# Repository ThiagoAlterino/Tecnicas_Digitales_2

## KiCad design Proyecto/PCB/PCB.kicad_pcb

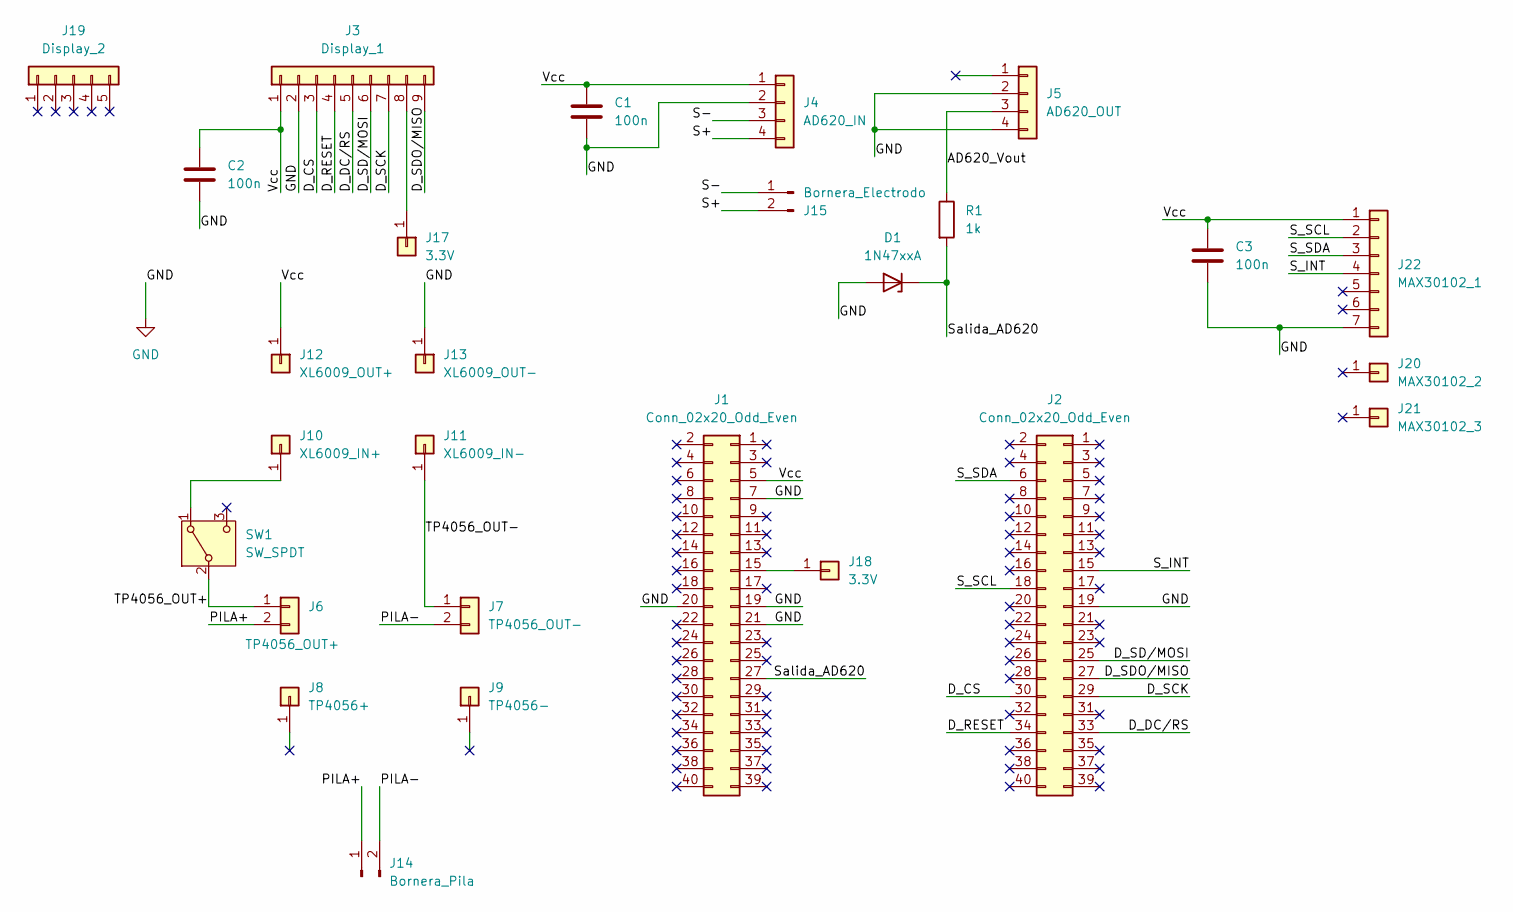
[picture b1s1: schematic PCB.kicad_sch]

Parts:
C1, C2, C3: 100n; C_Disc_D5.0mm_W2.5mm_P5.00mm
D1: 1N47xxA; D_DO-41_SOD81_P10.16mm_Horizontal
J1, J2: Conn_02x20_Odd_Even; PinSocket_2x20_P2.54mm_Vertical
J3: Display_1; PinSocket_1x09_P2.54mm_Vertical
J4: AD620_IN; PinSocket_1x04_P2.54mm_Vertical
J5: AD620_OUT; PinSocket_1x04_P2.54mm_Vertical
J6: TP4056_OUT+; PinSocket_1x02_P2.54mm_Vertical
J7: TP4056_OUT-; PinSocket_1x02_P2.54mm_Vertical
J8: TP4056+; PinSocket_1x01_P2.54mm_Vertical
J9: TP4056-; PinSocket_1x01_P2.54mm_Vertical
J10: XL6009_IN+; PinSocket_1x01_P2.54mm_Vertical
J11: XL6009_IN-; PinSocket_1x01_P2.54mm_Vertical
J12: XL6009_OUT+; PinSocket_1x01_P2.54mm_Vertical
J13: XL6009_OUT-; PinSocket_1x01_P2.54mm_Vertical
J14: Bornera_Pila; TerminalBlock_Phoenix_MKDS-1,5-2-5.08_1x02_P5.08mm_Horizont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
J15: Bornera_Electrodo; TerminalBlock_Phoenix_MKDS-1,5-2-5.08_1x02_P5.08mm_Horizont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
J17, J18: 3.3V; TestPoint_Pad_D2.0mm
J19: Display_2; PinSocket_1x05_P2.54mm_Vertical
J20: MAX30102_2; PinSocket_1x01_P2.54mm_Vertical
J21: MAX30102_3; PinSocket_1x01_P2.54mm_Vertical
J22: MAX30102_1; PinSocket_1x07_P2.54mm_Vertical
R1: 1k; R_Axial_DIN0207_L6.3mm_D2.5mm_P10.16mm_Horizontal
SW1: SW_SPDT; SW_Slide-03_Wuerth-WS-SLTV_10x2.5x6.4_P2.54mm

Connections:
/AD620_Vout: J5.3, R1.1
/D_CS: J2.30, J3.3
/D_DC/RS: J2.33, J3.5
/D_RESET: J2.34, J3.4
/D_SCK: J2.29, J3.7
/D_SDO/MISO: J2.27, J3.9
/D_SD/MOSI: J2.25, J3.6
/PILA+: J6.2, J14.1
/PILA-: J7.2, J14.2
/S+: J4.4, J15.2
/S-: J4.3, J15.1
/S_INT: J2.15, J22.4
/S_SCL: J2.18, J22.2
/S_SDA: J2.6, J22.3
/Salida_AD620: D1.1 (K), J1.27, R1.2
/TP4056_OUT+: J6.1, SW1.2 (B)
/TP4056_OUT-: J7.1, J11.1 (Pin_1_1)
/Vcc: C1.1, C2.1, C3.1, J1.5, J3.1, J4.1, J12.1 (Pin_1_1), J22.1
GND: C1.2, C2.2, C3.2, D1.2 (A), J1.7, J1.19, J1.20, J1.21, J2.19, J3.2, J4.2, J5.2, J5.4, J13.1 (Pin_1_1), J22.7
unnamed: J1.15, J18.1 (Pin_1_1)
unnamed: J10.1 (Pin_1_1), SW1.1 (A)
unnamed: J3.8, J17.1 (Pin_1_1)

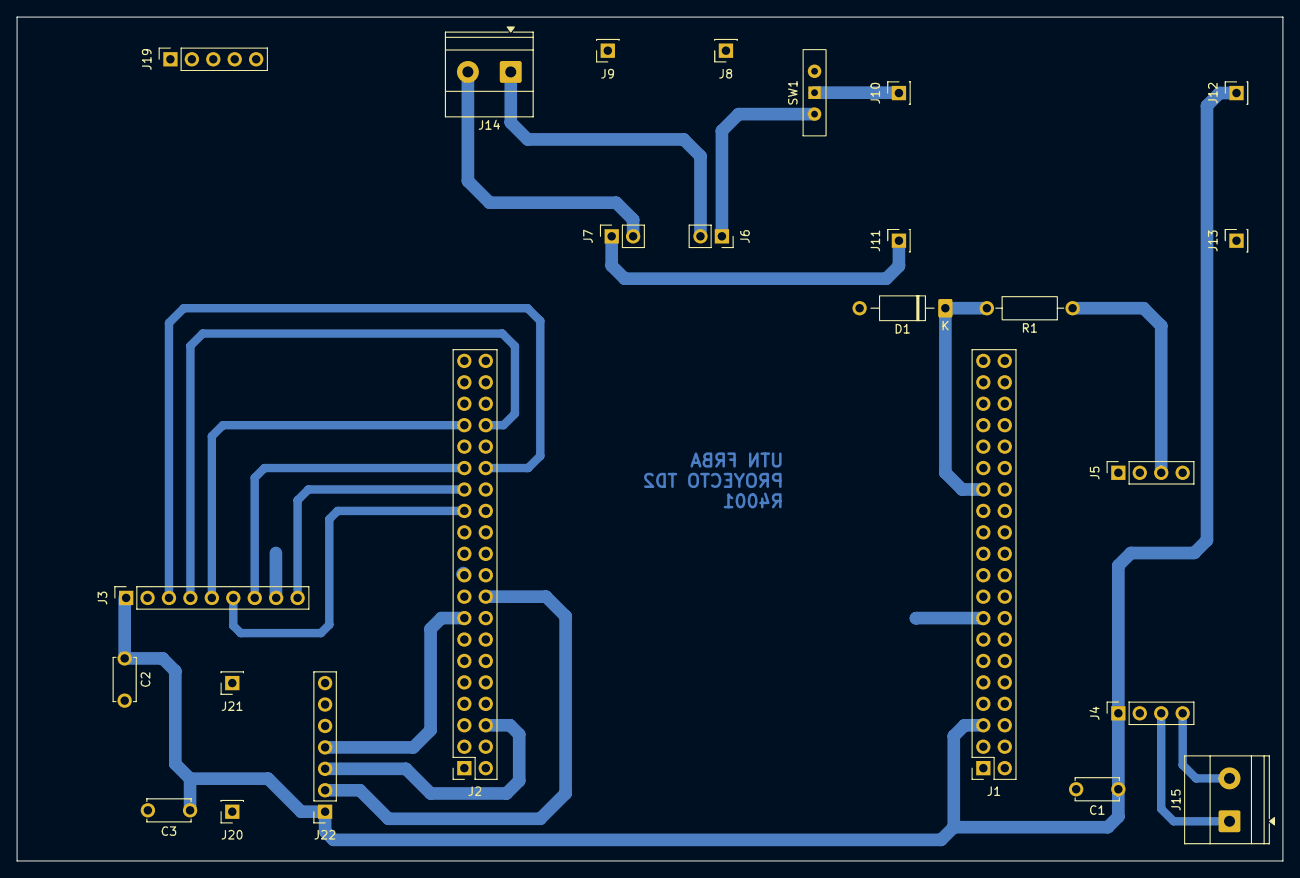
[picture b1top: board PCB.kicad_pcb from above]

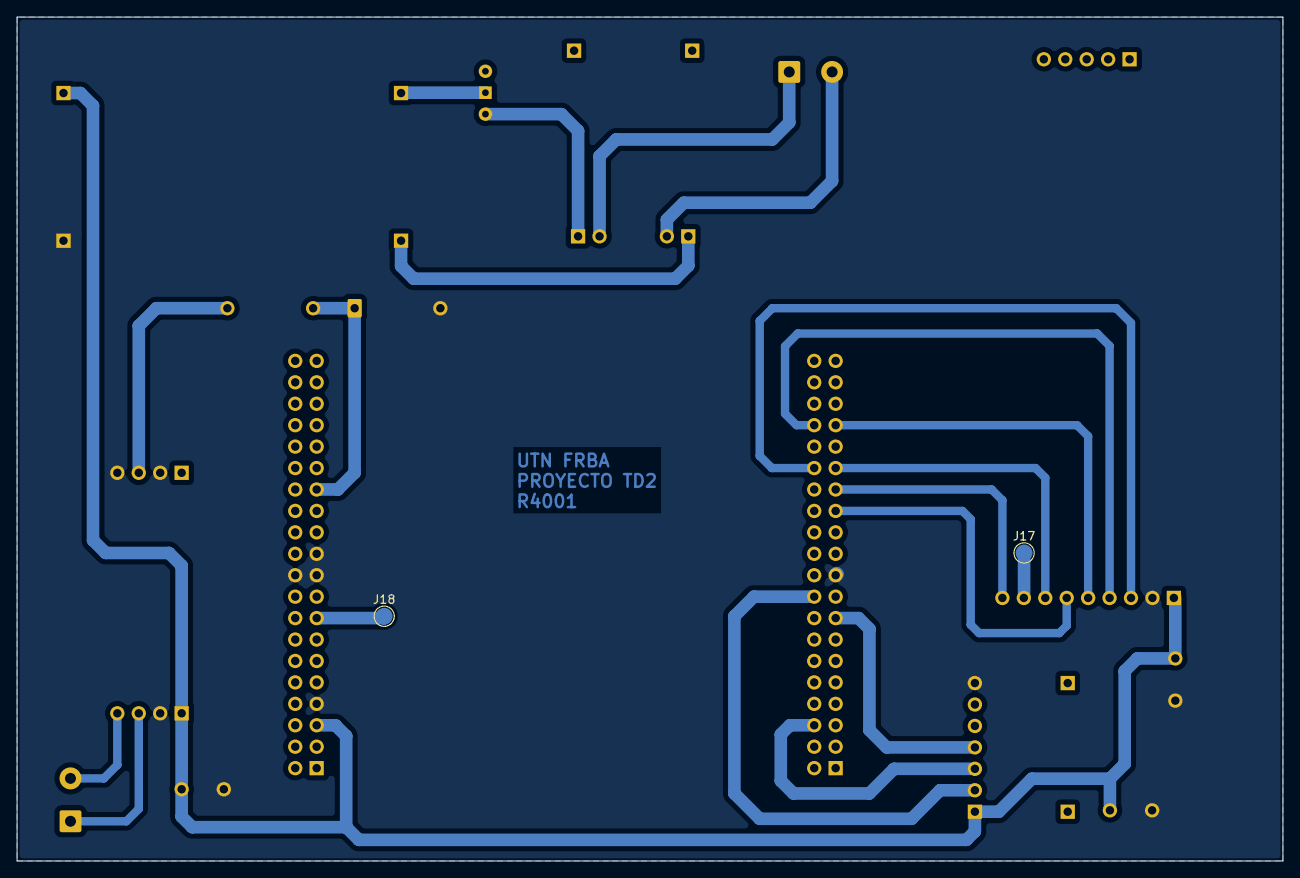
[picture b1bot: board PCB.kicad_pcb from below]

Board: 2 copper layers, 150.0 x 100.0 mm, 27 parts (2 on the bottom side), 22 nets.
